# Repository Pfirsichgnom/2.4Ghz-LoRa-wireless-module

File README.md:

## SX1280 2.4 GHz Diversity Transceiver  
This project is my attempt to design a compact, low-power 2.4 GHz transceiver PCB based on two Semtech SX1280 transceiver ICs. The goal is to create a small, affordable, and versatile wireless communication platform that supports experimenting with diversity techniques in both the frequency and spatial domains.  
The design uses two independent transceiver modules, allowing for redundancy through different operating frequencies or separate antennas. Particular attention has been paid to PCB layout, RF signal integrity, power distribution, and electromagnetic compatibility to achieve reliable wireless performance in a compact form factor.  
The project includes the schematics, PCB layout, and associated design files. It also serves as a learning experience in high-frequency PCB design, RF layout techniques, and the practical challenges of building a custom wireless transceiver.  
### Want to learn more about the design?  
A more detailed description of the project, including the design decisions and technical considerations, can be found on my website: https://www.transistorundko.com/electronics_hw/projects/lora_wireless_module_v1/index.html .
  
## License  
This project is available for personal, educational, and non-commercial research purposes. Commercial use requires prior written permission from the copyright holder. Please refer to the LICENSE file for the complete terms and conditions.

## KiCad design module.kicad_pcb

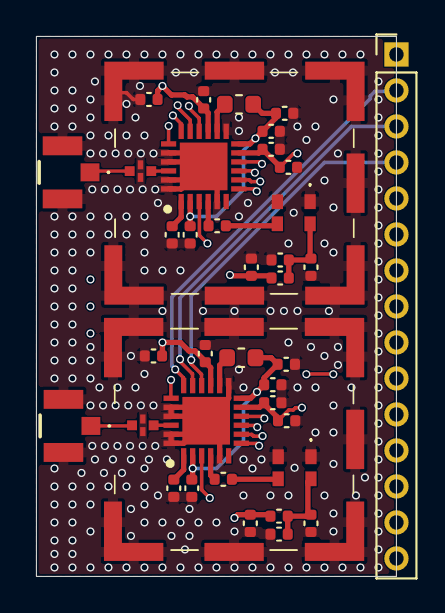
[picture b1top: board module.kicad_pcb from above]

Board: 4 copper layers, 20.0 x 30.0 mm, 39 parts (0 on the bottom side), 33 nets.

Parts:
C1, C16: 1n; C_0402_1005Metric
C2, C3, C11, C12: C; C_0402_1005Metric
C4, C7, C17, C18: 10n; C_0402_1005Metric
C5, C10, C13, C19, C21, C22, C32, C33: 100n; C_0402_1005Metric
C6, C20: 470n; C_0402_1005Metric
C8, C9, C14, C15: 10u; C_0402_1005Metric
FB1, FB2: FerriteBead; C_0402_1005Metric
FL1, FL2: 2450FM07D0034001T
H1, H2: 3610213126S
IC1, IC2: SX1280IMLTRT; QFN50P400X400X100-25N-D
J1, J2: CONUFL001-SMD-T; CONUFL001SMDT
J4: Conn_01x15_Socket; PinHeader_1x15_P2.00mm_Vertical
L1, L2: 15u; L_0603_1608Metric
Y1, Y2: ECS-TXO-20CSMV4-520-AN-TR; ECSTXO20CSMV4520ANTR

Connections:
3V3: C8.2, C9.2, C10.2, C13.2, C14.2, C15.2, C21.2, C22.2, C32.2, C33.2, FB1.1, FB2.1, IC1.11 (VBAT_IO), IC1.15 (VBAT), IC2.11 (VBAT_IO), IC2.15 (VBAT)
/BUSY_1: IC1.7 (BUSY), J4.8
/BUSY_2: IC2.7 (BUSY), J4.14
/IRQ_1: IC1.10 (DIO3), J4.5
/IRQ_2: IC1.9 (DIO2), J4.6
/IRQ_3: IC1.8 (DIO1), J4.7
/IRQ_4: IC2.10 (DIO3), J4.11
/IRQ_5: IC2.9 (DIO2), J4.12
/IRQ_6: IC2.8 (DIO1), J4.13
/MISO: IC1.16 (MISO_TX), IC2.16 (MISO_TX), J4.4
/MOSI: IC1.17 (MOSI_RX), IC2.17 (MOSI_RX), J4.3
/NRESET_1: IC1.3 (NRESET), J4.9
/NRESET_2: IC2.3 (NRESET), J4.15
/NSS_1: IC1.19 (NSS_CTS), J4.1
/NSS_2: IC2.19 (NSS_CTS), J4.10
/SCK: IC1.18 (SCK_RTSN), IC2.18 (SCK_RTSN), J4.2
GND: C2.1, C3.1, C4.1, C5.1, C6.1, C7.1, C8.1, C9.1, C10.1, C11.1, C12.1, C13.1, C14.1, C15.1, C17.1, C18.1, C19.1, C20.1, C21.1, C22.1, C32.1, C33.1, FL1.2 (GND_1), FL1.4 (GND_2), FL2.2 (GND_1), FL2.4 (GND_2), H1.1, H1.2, H1.3, H1.4, H1.5, H1.6, H1.7, H1.8, H1.9, H1.10, H1.12, H2.1, H2.2, H2.3, H2.4, H2.5, H2.6, H2.7, H2.8, H2.9, H2.10, H2.12, IC1.5 (GND_1), IC1.13 (GND_2), IC1.20 (GND_3), IC1.21 (GND_4), IC1.23 (GND_5), IC1.24 (GND_6), IC1.25 (EP), IC2.5 (GND_1), IC2.13 (GND_2), IC2.20 (GND_3), IC2.21 (GND_4), IC2.23 (GND_5), IC2.24 (GND_6), IC2.25 (EP), J1.2 (GND_1), J1.3 (GND_2), J2.2 (GND_1), J2.3 (GND_2), Y1.1 (GROUND_1), Y1.2 (GROUND_2), Y2.1 (GROUND_1), Y2.2 (GROUND_2)
unnamed: FL1.1 (IN), IC1.22 (RFIO)
unnamed: FL1.3 (OUT), J1.1 (SIG)
unnamed: FL2.1 (IN), IC2.22 (RFIO)
unnamed: FL2.3 (OUT), J2.1 (SIG)
unnamed: C4.2, C5.2, C6.2, IC1.2 (VDD_IN), IC1.12 (DCC_FB), L1.2
unnamed: IC1.14 (DCC_SW), L1.1
unnamed: C7.2, IC1.1 (VR_PA)
unnamed: C1.2, IC1.4 (XTA)
unnamed: C18.2, C19.2, C20.2, IC2.2 (VDD_IN), IC2.12 (DCC_FB), L2.2
unnamed: IC2.14 (DCC_SW), L2.1
unnamed: C17.2, IC2.1 (VR_PA)
unnamed: C16.2, IC2.4 (XTA)
unnamed: C1.1, Y1.3 (OUTPUT)
unnamed: C2.2, C3.2, FB1.2, Y1.4 (VDD)
unnamed: C16.1, Y2.3 (OUTPUT)
unnamed: C11.2, C12.2, FB2.2, Y2.4 (VDD)
